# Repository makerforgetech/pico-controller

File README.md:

# pico-controller

This project is a wifi enabled controller module, and includes an uninterruptable power supply (UPS) and a custom PCB utilising the Raspberry Pi Pico. 
The controller is designed to be used in a variety of applications and the hardware includes an array of neopixels, connected in series to allow for a variety of lighting effects.

Note: This is in active development and is not yet ready for community adoption. Please be patient and check back for updates.

## Features

- Joystick control of neopixels
- Wifi integration
- UPS modules
- Custom PCB
- Neopixel array
- 18650 battery management

## Bill of Materials

| Part | Quantity | Description | Link |
| --- | --- | --- | --- |
| 18650 battery | 1 | 3.7V 18650 battery | - |
| 18650 UPS module | 1 | 18650 battery shield | [Link](https://www.wildware.net/products/18650-battery-shield) |
| Neopixel LED strip | 2 | 5V neopixel LED strip | - |
| Raspberry Pi Pico | 1 | Raspberry Pi Pico | [Link](https://www.raspberrypi.org/products/raspberry-pi-pico/) |
| Magnetic connectors (4 pin) | 3 pairs | Allows data and power connection between modules | - |
| Magnetic connectors (2 pin) | 1 pair | Allows power connection between power cell and base unit for charging | - |
| Toggle push switch with LED | 1 | Toggle push switch with LED | - |
| Wires | - | Various colours and lengths | - |
| Neopixel Ring | 1 | 8 LED neopixel ring | - |
| Neopixel Jewel | 1 | 7 LED neopixel jewel | - |
| Neopixel Module | 1 | 1 LED neopixel module | - |
| 3D printed parts | various | 3D printed parts | - |
| Joystick module | 1 | Joystick module | - |
| Microwave sensor | 1 | Microwave sensor | - |
| Momentary push button | 1 | Momentary push button | - |
| Custom PCB | 1 | Custom PCB | See PCB folder |

## UPS Wiring

## Pico Controller PCB

[PCB Files - KiCad](https://github.com/makerforgetech/pico-controller/tree/main/PCB/PicoController)

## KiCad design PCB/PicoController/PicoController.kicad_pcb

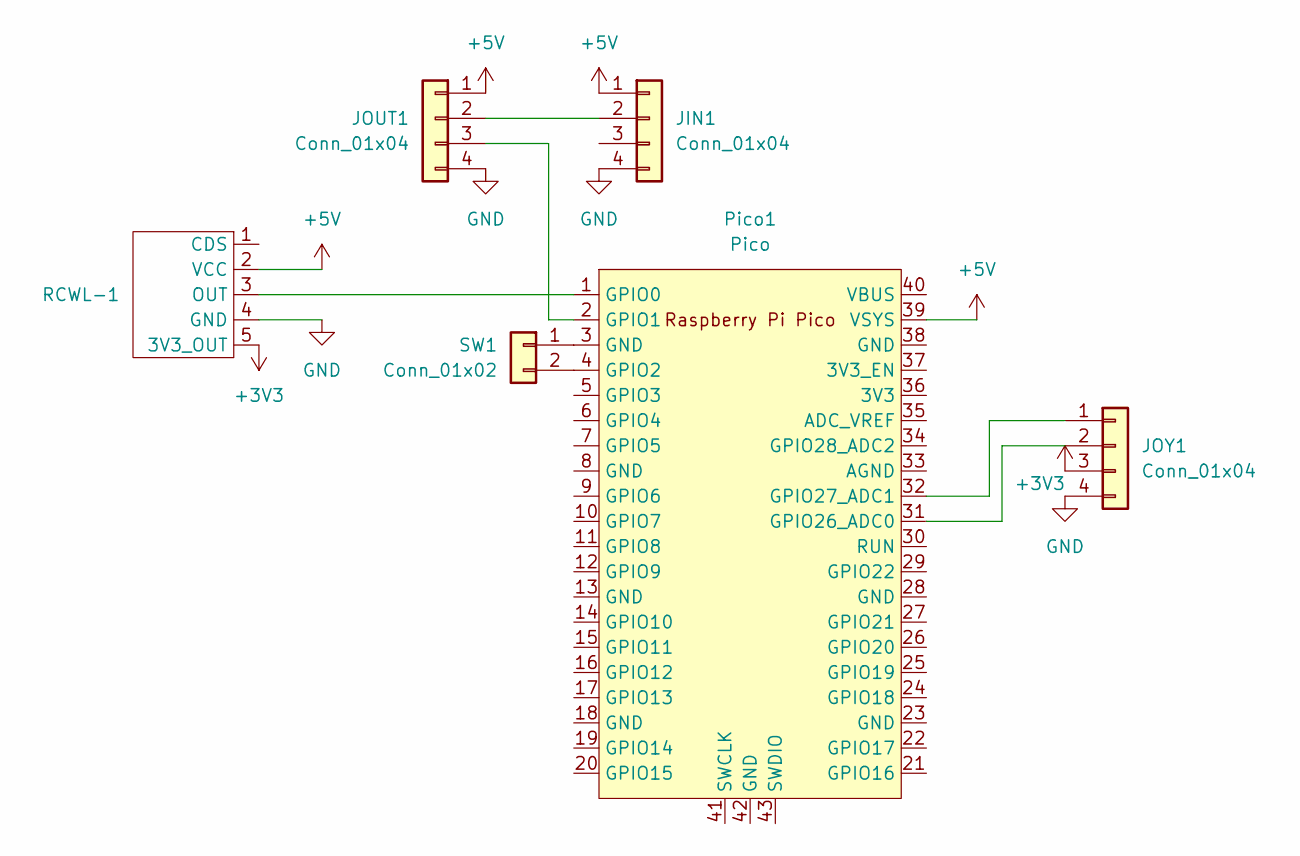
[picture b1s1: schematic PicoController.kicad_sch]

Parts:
JIN1: Conn_01x04; PinHeader_1x04_P2.54mm_Vertical
JOUT1: Conn_01x04; PinHeader_1x04_P2.54mm_Vertical
JOY1: Conn_01x04; PinHeader_1x04_P2.54mm_Vertical
Pico1: Pico; RPi_Pico_SMD_TH
RCWL-1: RCWL-0516
SW1: Conn_01x02; PinHeader_1x02_P2.54mm_Vertical

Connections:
+3V3: JOY1.3, RCWL-1.5 (3V3_OUT)
+5V: JIN1.1, JOUT1.1, Pico1.39 (VSYS), RCWL-1.2 (VCC)
GND: JIN1.4, JOUT1.4, JOY1.4, RCWL-1.4 (GND)
unnamed: JIN1.2, JOUT1.2
unnamed: JOUT1.3, Pico1.2 (GPIO1)
unnamed: JOY1.1, Pico1.32 (GPIO27_ADC1)
unnamed: JOY1.2, Pico1.31 (GPIO26_ADC0)
unnamed: Pico1.1 (GPIO0), RCWL-1.3 (OUT)
unnamed: Pico1.4 (GPIO2), SW1.2
unnamed: Pico1.3 (GND), SW1.1

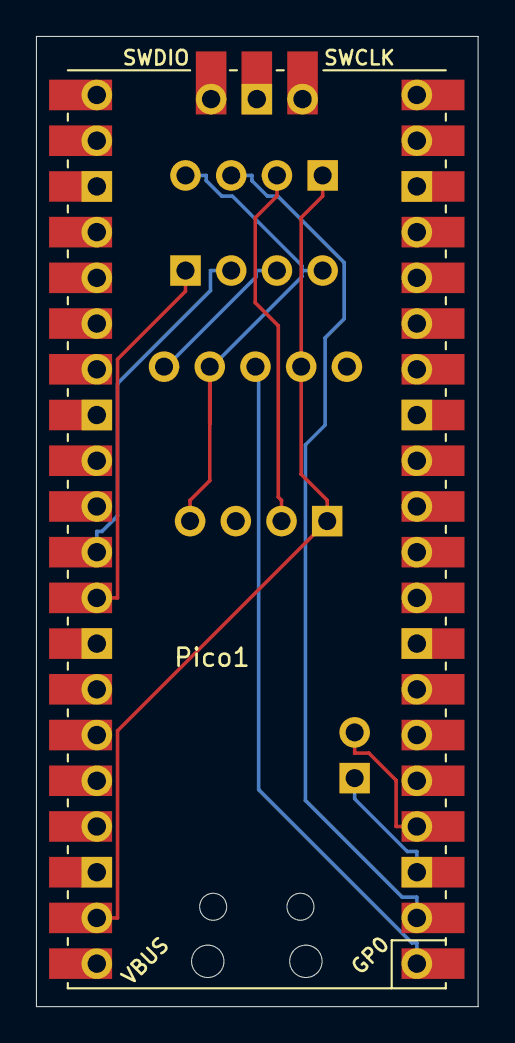
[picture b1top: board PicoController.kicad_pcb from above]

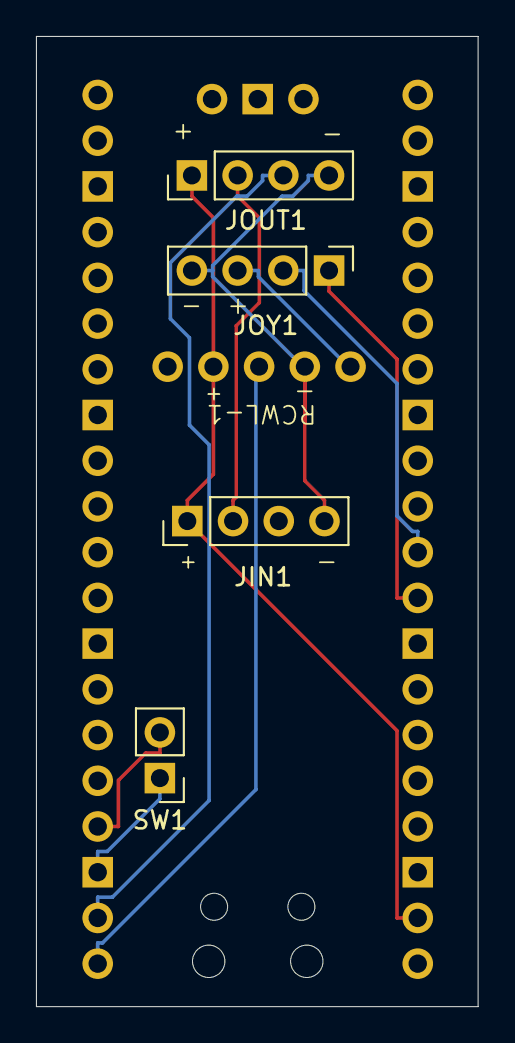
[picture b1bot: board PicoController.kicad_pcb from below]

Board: 2 copper layers, 24.5 x 53.9 mm, 6 parts (5 on the bottom side), 10 nets.

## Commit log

2024-11-29 Improve colours and thumbstick input
2024-11-30 Basic button behaviour
